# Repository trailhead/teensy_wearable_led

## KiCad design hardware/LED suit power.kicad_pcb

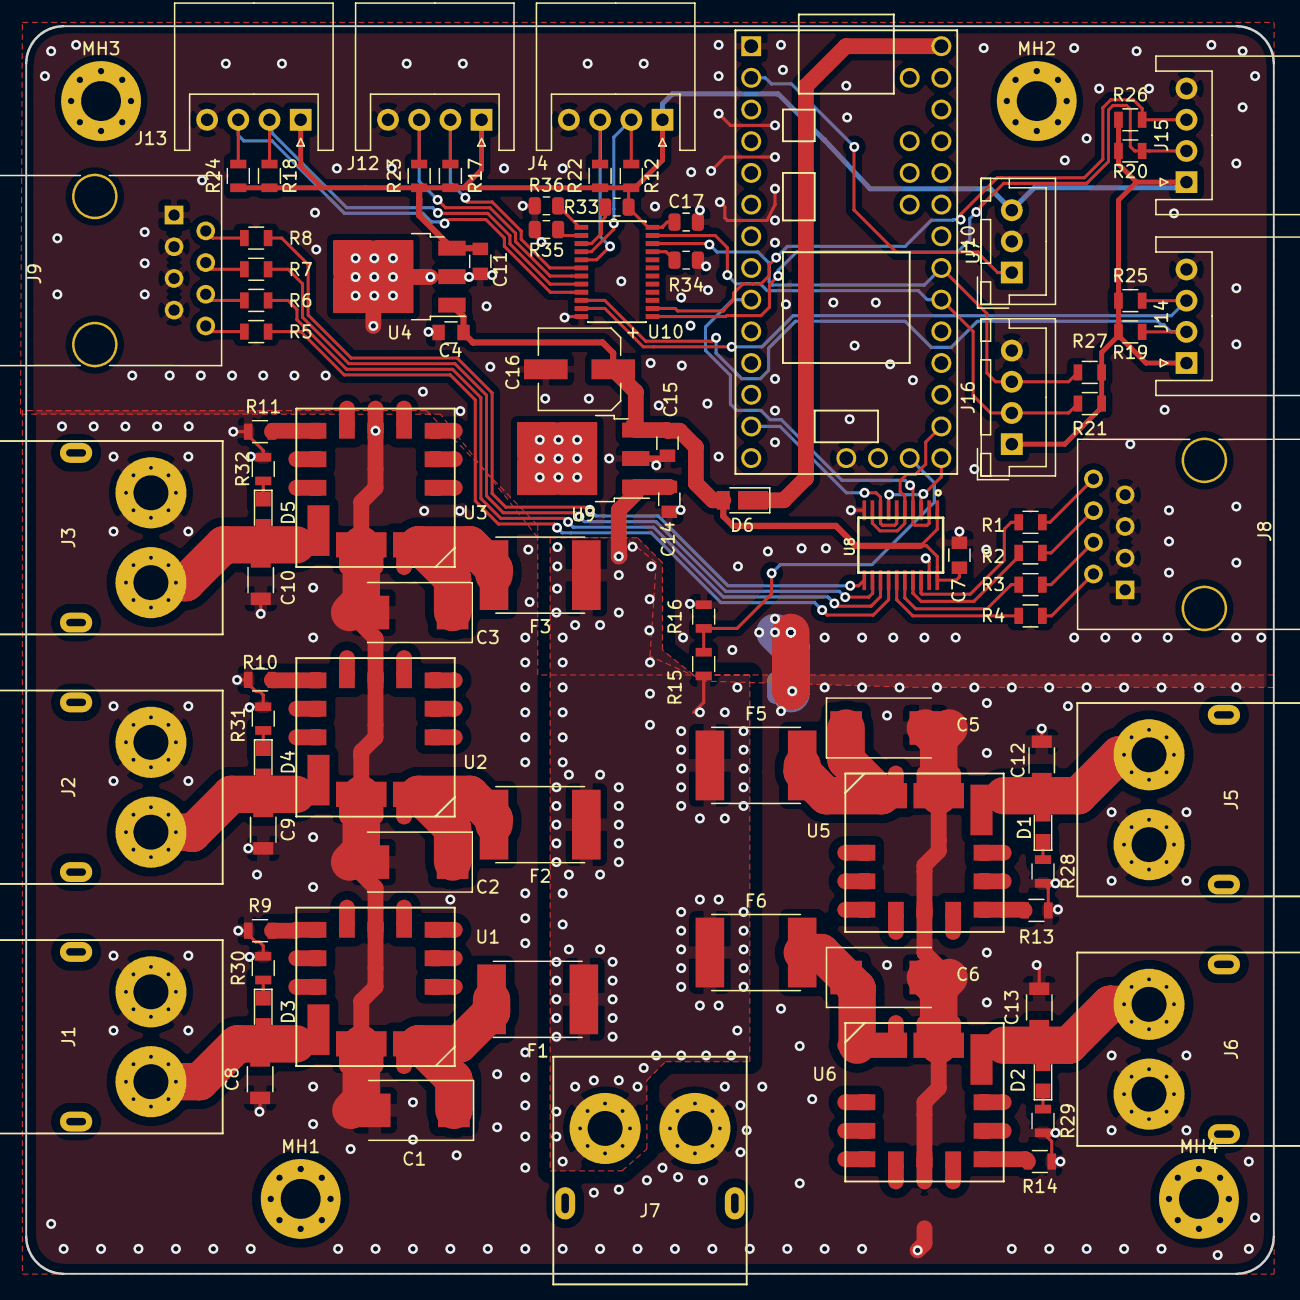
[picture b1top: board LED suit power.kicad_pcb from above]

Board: 2 copper layers, 100.0 x 100.0 mm, 93 parts (0 on the bottom side), 63 nets.

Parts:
C1, C2, C3, C5, C6: CP_Small; CP_Tantalum_Case-D_EIA-7343-31_Reflow
C4, C14: 0.33uF; C_0805
C7: C_Small; C_0805
C8, C9, C10, C12, C13: C_Small; C_1206
C11, C15: 0.1uF; C_0805
C16: CP_Small; CP_Elec_6.3x5.8
C17: 10uF; C_0805_2012Metric
D1, D2, D3, D4, D5: LED; LED_0805
D6: D_Schottky; D_PowerDI-123
F1, F2, F3, F5, F6: Polyfuse_Small; Fuse_SMD2920
J1, J2, J3, J5, J6: XT-60; XT-60flipped
J4, J12, J13, J14, J15: Conn_01x04_Male; JST_XH_S04B-XH-A_04x2.50mm_Angled
J7: XT-60
J8, J9: RJ45; RJ45_8
J10: Conn_01x03_Male; JST_XH_B03B-XH-A_03x2.50mm_Straight
J16: Conn_01x04_Male; JST_XH_B04B-XH-A_04x2.50mm_Straight
MH1, MH2, MH3, MH4: MountingHole_Pad; MountingHole_3.2mm_M3_Pad_Via
R1, R2, R3, R4, R5, R6, R7, R8, R9, R10, R11, R13, R14, R15, R16, R28, R29, R30, R31, R32: R_Small; R_0805
R12, R17, R18, R19, R20, R21, R22, R23, R24, R25, R26, R27: 1k; R_0805
R33, R34, R35, R36: 10k; R_0805_2012Metric
U1, U2, U3, U5, U6: OKL2-T_6-W12P-C; OKL2-T 6-W12P-C
U4: L7833; TO-252-3_TabPin2
U7: Teensy3.2; Teensy32_mine
U8: 74HCT245; TSSOP20
U9: L7805; TO-252-3_TabPin2
U10: TCA9548APWR; TSSOP-24_4.4x7.8mm_P0.65mm

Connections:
+3V3: C11.1, C17.1, J4.1, J10.3, J12.1, J13.1, J14.1, J15.1, J16.1, R12.2, R17.2, R18.2, R19.2, R20.2, R21.2, R22.2, R23.2, R24.2, R25.2, R26.2, R27.2, R33.2, U4.3, U10.24
+5V: C4.1, C7.1, C15.1, C16.1, D6.2, U4.1, U8.1, U8.20, U9.3
BATT_LEVEL: R15.2, R16.1, U7.19
GND: C1.2, C2.2, C3.2, C4.2, C5.2, C6.2, C7.2, C8.1, C9.2, C10.2, C11.2, C12.2, C13.2, C14.2, C15.2, C16.2, C17.2, J1.2, J2.2, J3.2, J4.4, J5.2, J6.2, J7.2, J8.1, J8.3, J8.5, J8.7, J9.1, J9.3, J9.5, J9.7, J10.2, J12.4, J13.4, J14.4, J15.4, J16.4, R9.2, R10.2, R11.2, R13.2, R14.2, R16.2, R28.2, R29.2, R30.2, R31.2, R32.2, R34.2, R35.2, R36.2, U1.3, U1.7, U2.3, U2.7, U3.3, U3.7, U4.2, U5.3, U5.7, U6.3, U6.7, U7.1, U7.17, U8.10, U8.19, U9.2, U10.12
unnamed: C1.1, F1.2, U1.2
unnamed: C2.1, F2.2, U2.2
unnamed: C3.1, F3.2, U3.2
unnamed: C5.1, F5.2, U5.2
unnamed: C6.1, F6.2, U6.2
unnamed: C8.2, D3.2, J1.1, U1.4
unnamed: C9.1, D4.2, J2.1, U2.4
unnamed: C10.1, D5.2, J3.1, U3.4
unnamed: C12.1, D1.2, J5.1, U5.4
unnamed: C13.1, D2.2, J6.1, U6.4
unnamed: D1.1, R28.1
unnamed: D2.1, R29.1
unnamed: D3.1, R30.1
unnamed: D4.1, R31.1
unnamed: D5.1, R32.1
unnamed: D6.1, U7.33
unnamed: J4.2, R12.1, U10.4
unnamed: J4.3, R22.1, U10.5
unnamed: J8.2, R4.1
unnamed: J8.4, R3.1
unnamed: J8.6, R2.1
unnamed: J8.8, R1.1
unnamed: J9.2, R8.1
unnamed: J9.4, R7.1
unnamed: J9.6, R6.1
unnamed: J9.8, R5.1
unnamed: J12.2, R17.1, U10.6
unnamed: J12.3, R23.1, U10.7
unnamed: J13.2, R18.1, U10.8
unnamed: J13.3, R24.1, U10.9
unnamed: J14.2, R19.1, U10.10
unnamed: J14.3, R25.1, U10.11
unnamed: J15.2, R20.1, U10.13
unnamed: J15.3, R26.1, U10.14
unnamed: R1.2, U8.18
unnamed: R2.2, U8.17
unnamed: R3.2, U8.16
unnamed: R4.2, U8.15
unnamed: R5.2, U8.14
unnamed: R6.2, U8.13
unnamed: R7.2, U8.12
unnamed: R8.2, U8.11
unnamed: R9.1, U1.6
unnamed: R10.1, U2.6
unnamed: R11.1, U3.6
unnamed: R13.1, U5.6
unnamed: R14.1, U6.6
unnamed: R33.1, U10.3
unnamed: R34.1, U10.21
unnamed: R35.1, U10.2
unnamed: R36.1, U10.1
PIN0: J10.1, U7.2
PIN7: U7.9, U8.2, U8.4
PIN11: U7.13, U8.6, U8.8
PIN13: U7.20, U8.3, U8.7
PIN14: U7.21, U8.5, U8.9
PIN18: J16.2, R21.1, U7.25, U10.23
PIN19: J16.3, R27.1, U7.26, U10.22
VIN: C14.1, F1.1, F2.1, F3.1, F5.1, F6.1, J7.1, R15.1, U9.1

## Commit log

2018-10-16 reassigned pins for apa102 conversion
2019-10-13 i2c expander
2019-10-13 moved into hardware folder
2019-10-13 added firmware files

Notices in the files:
hardware/LED suit power.kicad_pcb:
(C) 2018 Chris Miller
